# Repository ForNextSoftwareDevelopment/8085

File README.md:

# 8085
Intel 8085 Assembler / Disassembler / Simulator

This is an assembler/disassembler for the Intel-8085 microprocessor.
It can also simulate an Intel SDK-85 developers board (keyboard/display).

Copyright (c) 2022 Dirk Prins

Permission is hereby granted, free of charge, to any person obtaining a copy of this software and associated documentation files (the "Software"), to deal in the Software without restriction, including without limitation the rights to use, copy, modify, merge, publish, distribute, sublicense, and/or sell copies of the Software, and to permit persons to whom the Software is furnished to do so, subject to the following conditions:

The above copyright notice and this permission notice shall be included in all copies or substantial portions of the Software.

THE SOFTWARE IS PROVIDED "AS IS", WITHOUT WARRANTY OF ANY KIND, EXPRESS OR IMPLIED, INCLUDING BUT NOT LIMITED TO THE WARRANTIES OF MERCHANTABILITY, FITNESS FOR A PARTICULAR PURPOSE AND NONINFRINGEMENT. IN NO EVENT SHALL THE AUTHORS OR COPYRIGHT HOLDERS BE LIABLE FOR ANY CLAIM, DAMAGES OR OTHER LIABILITY, WHETHER IN AN ACTION OF CONTRACT, TORT OR OTHERWISE, ARISING FROM, OUT OF OR IN CONNECTION WITH THE SOFTWARE OR THE USE OR OTHER DEALINGS IN THE SOFTWARE.

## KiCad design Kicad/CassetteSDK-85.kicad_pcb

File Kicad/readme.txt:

This is the schematics from the AP-29 document for the data cassette interface.
2 leds have been added to be able to monitor the data.

The pcb design has been made with a homemade mind.

The backside of the pcb is all 'ground'.
The components are placed (mostly surface mounted) on the 'front' side.

Feel free to change (or make your own) pcb design.

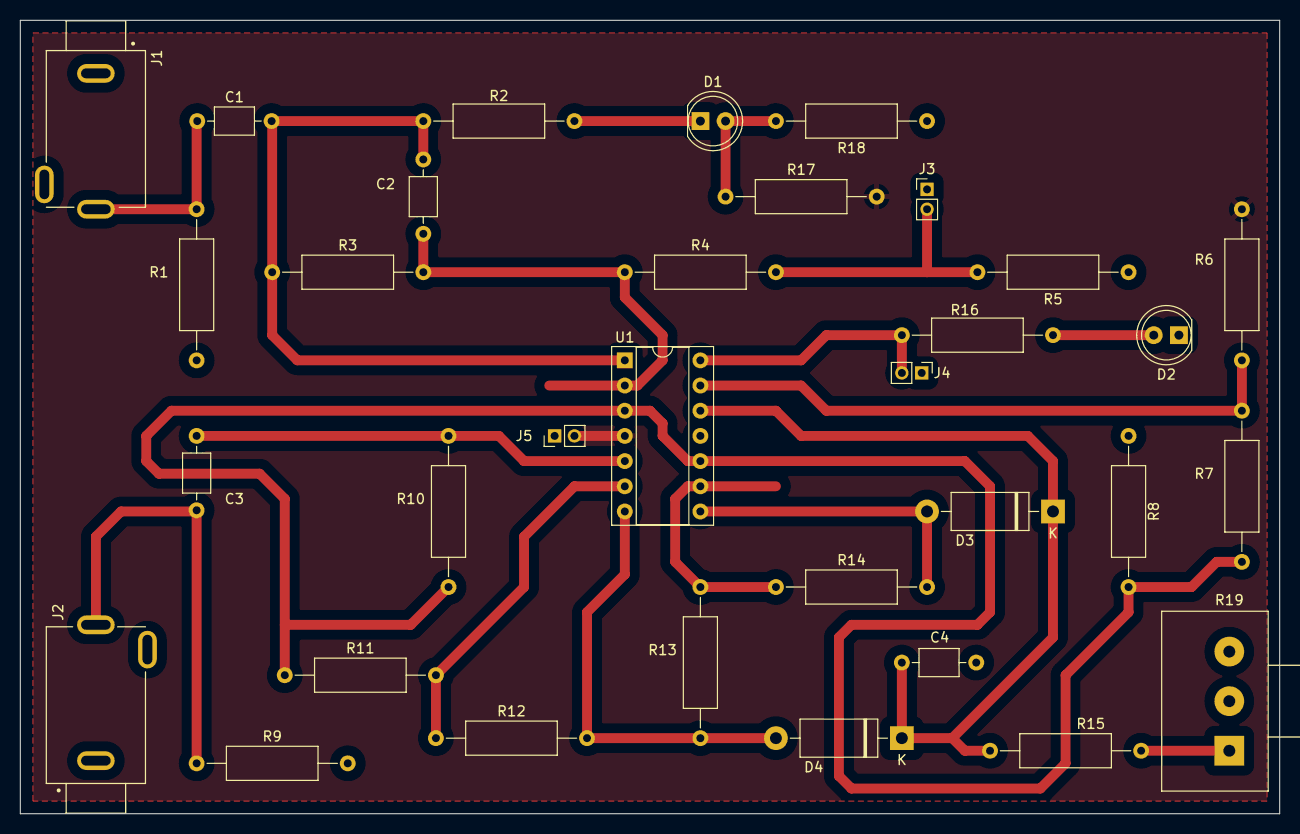
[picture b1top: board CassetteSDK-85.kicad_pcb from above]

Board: 2 copper layers, 127.0 x 80.0 mm, 33 parts (0 on the bottom side), 20 nets.

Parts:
C1, C3, C4: 100n; C_Axial_L3.8mm_D2.6mm_P7.50mm_Horizontal
C2: 1n; C_Axial_L3.8mm_D2.6mm_P7.50mm_Horizontal
D1, D2: LED; LED_D5.0mm
D3, D4: 1N60; D_DO-15_P12.70mm_Horizontal
J1, J2: MJ-3536N; CUI_MJ-3536N
J3: SOD; PinHeader_1x02_P2.00mm_Vertical
J4: SID; PinHeader_1x02_P2.00mm_Vertical
J5: Power; PinHeader_1x02_P2.00mm_Vertical
R1, R6, R9, R15, R18: 1K; R_Axial_DIN0309_L9.0mm_D3.2mm_P15.24mm_Horizontal
R2, R7: 200; R_Axial_DIN0309_L9.0mm_D3.2mm_P15.24mm_Horizontal
R3, R5, R11, R12, R13, R14: 10K; R_Axial_DIN0309_L9.0mm_D3.2mm_P15.24mm_Horizontal
R4: 20K; R_Axial_DIN0309_L9.0mm_D3.2mm_P15.24mm_Horizontal
R8: 820; R_Axial_DIN0309_L9.0mm_D3.2mm_P15.24mm_Horizontal
R10: 1M; R_Axial_DIN0309_L9.0mm_D3.2mm_P15.24mm_Horizontal
R16: 330; R_Axial_DIN0309_L9.0mm_D3.2mm_P15.24mm_Horizontal
R17: 100; R_Axial_DIN0309_L9.0mm_D3.2mm_P15.24mm_Horizontal
R19: 10K; Potentiometer_Alps_RK163_Single_Horizontal
U1: LM324A; DIP-14_W7.62mm_Socket

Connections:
+5V: J5.2, R6.1, R17.2, U1.4 (V+)
GND: C4.1, D2.1 (K), J1.1, J1.3, J2.1, J2.3, J3.1, J4.1, J5.1, R1.2, R5.1, R8.2, R9.2, R18.1, R19.2, U1.11 (V-)
unnamed: C1.1, J1.2, R1.1
unnamed: C1.2, C2.1, R2.2, R3.1, U1.1
unnamed: C3.1, J2.2, R9.1
unnamed: D1.2 (A), R17.1, R18.2
unnamed: D1.1 (K), R2.1
unnamed: D2.2 (A), R16.2
unnamed: D3.2 (A), R14.2, U1.8
unnamed: C4.2, D3.1 (K), D4.1 (K), R15.1, U1.12 (+)
unnamed: D4.2 (A), R12.2, R13.1, U1.7
unnamed: R15.2, R19.1
unnamed: R7.2, R8.1, R10.1, R11.1, U1.3 (+), U1.10 (+)
unnamed: C2.2, R3.2, R4.1, U1.2 (-)
unnamed: C3.2, R10.2, U1.5 (+)
unnamed: R11.2, R12.1, U1.6 (-)
unnamed: R13.2, R14.1, U1.9 (-)
unnamed: R6.2, R7.1, U1.13 (-)
SID: J4.2, R16.1, U1.14
SOD: J3.2, R4.2, R5.2

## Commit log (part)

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2022-07-28 Create temp
2022-07-28 Add files via upload
    Initial Upload
2022-07-29 Add files via upload
    Version 1.1
2022-07-30 Add files via upload
    Update 1.2
2022-07-30 Add files via upload
    Version 1.2
2022-08-02 Add files via upload
    Update 1.3
2022-08-16 Version 1.5
2022-09-07 Version 1.6
2022-11-25 Version 1.7
2022-12-12 Version 1.8
2023-01-09 Version 1.9
2023-02-02 Version 2.0
2023-03-23 Version 2.1
